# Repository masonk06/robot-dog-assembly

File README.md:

# Luca — RoboDog quadruped

A custom 3D-printed, 12-actuator quadruped built to investigate the path from
CAD and learned locomotion in simulation to calibrated physical motion.
This repository connects mechanical design, embedded telemetry, actuator
calibration, GPU reinforcement learning, and sim-to-real diagnostics.

**Current milestone:** slow walking in simulation and supported hardware
motion experiments. Full-body unsupported walking and closed-loop hardware
policy deployment are not yet validated.

[Sim-to-real comparison](#sim-to-real-evidence) ·
[Hardware and software](#hardware-and-software-stack) ·
[Calibration workflow](#calibration-and-hardware-workflow) ·
[Next steps](#next-engineering-milestones) ·
[Portfolio summary](docs/PORTFOLIO.md) ·
[Policy architecture](docs/POLICY_ARCHITECTURE.md)

## Ground-contact diagnostic — October 30, 2026

A 10-second excerpt at original speed from the temporary prototype's ground-contact
test. This records experimental stepping and contact behavior; unsupported walking
and closed-loop hardware policy deployment are not yet validated.
[Full diagnostic recording](docs/sim-to-real/raw/supported-ground-diagnostic-20261030.mov)

## Simulation and supported hardware comparison

[Watch the full comparison](docs/sim-to-real/simulation-vs-real.mp4) ·
[Recording context](docs/sim-to-real/README.md)

The simulation body is fixed and the physical robot is supported. The clips
are not phase-synchronized: they illustrate joint motion, not measured tracking
accuracy or unsupported walking.

## Engineering overview

The project follows a measurement-driven loop: build the mechanism, establish
joint correspondence, compare commanded and measured motion, identify model
gaps, and evaluate revised controllers in simulation before expanding hardware
tests.

- **Mechanical integration:** Fusion assemblies, printable geometry, placement
  tools, and successive electronics-packaging revisions.
- **Calibration and telemetry:** explicit servo IDs, model-zero captures,
  signed encoder correspondence, conservative limits, and a read-only live
  mirror between physical joints and the simulation.
- **Learning and simulation:** a four-beat reference gait with small learned
  residuals; MuJoCo/Newton validation and a CUDA PPO pipeline covering physics,
  observations, rewards, normalization, GAE, and optimizer updates.
- **Transfer diagnostics:** supported joint-tracking logs, IMU bring-up,
  controlled COM/contact experiments, and a separate robust quasi-static
  crawl development track.

### Results and validation boundaries

| Area | Recorded result | What remains unproven |
| --- | --- | --- |
| Preserved walking benchmark | About **16.02 cm forward in 20 s**, six steps per leg, with no falls/sliding resets across three simulation trials | Broad robustness or physical walking; this is a limited historical benchmark |
| GPU training | CUDA pipeline tested locally and on an OSU H100 allocation; selected checkpoints retain normalization and source archives | Training throughput alone does not establish gait quality or transfer |
| Supported hardware transfer | Rear-left IDs 8/9 progressed through small-angle and full-amplitude replay; the faster 46.2 s trial completed with verified torque release | All-leg calibration, ground balance, or feedback-policy deployment |
| IMU bring-up | ESP32 readout identified an MPU6500-compatible device; stationary reference and gyro-bias estimate saved | Full sensor calibration, robot-axis alignment, and policy-ready body-state estimation |
| Robust crawl | Separate simulation preset and scenario curriculum implemented | A validated robust-crawl result on the final robot |

The walking benchmark is documented in the [October 26 status snapshot](docs/STATUS.md)
and [preserved policies](policies/README.md). Later successor-policy diagnostics
have different conditions and should be read separately.

## Hardware and software stack

| Layer | Components and role |
| --- | --- |
| Mechanism | Custom printed quadruped, 12 STS3215 bus servos; Fusion snapshots and STL/STEP assets in [CAD](cad/README.md) |
| Servo bus | Waveshare Bus Servo Adapter (A), 12 V servo supply; historical PC serial tools and current ESP32 telemetry workflow |
| Embedded controller | NodeMCU ESP32S; servo UART on GPIO17 TX / GPIO16 RX; USB CSV telemetry normally on COM7 at 115200 baud |
| Inertial sensing | MPU6500-compatible device at I2C address 0x68, using GPIO21/22; [bring-up and reference capture](hardware/imu/README.md) |
| Calibration tools | Python viewers, timestamped zero/direction/limit records, encoder-to-model conversion, and read-only live mirroring |
| Simulation | MuJoCo robot model; Newton GPU physics and validation tools |
| Learning | PPO with a 60-value observation contract and 12 actions; 50 Hz control with learned residuals limited to about 2° in the preserved v7 controller |
| Reproducibility | Python 3.12, pinned CPU/CUDA dependency sets, W&B run tracking, frozen policy sources and normalization backups |

Final chassis, battery, power distribution, and onboard-compute integration
remain in development. Packaging CAD is revision-specific and does not
automatically update the simulation's mass, inertias, or joint geometry.

## Calibration and hardware workflow

Start with the [current hardware sequence](hardware/GETTING_DOG_RUNNING.md).
The newer ESP32 calibration records and older PC-driven rear-left replay
describe different stages of the prototype; historical successful motion
does not make the new frame ready for full-body replay.

1. **Confirm identity and zero pose.** Use the current joint map and
   [zero-point procedure](hardware/ESP32_ZERO_CHECK.md). Approximate model zeros
   live in [zero-points-current.json](hardware/calibrations/zero-points-current.json);
   they are not generic factory centers.
2. **Capture directions and conservative endpoints.** Follow the
   [ESP32 direction/limit checker](hardware/ESP32_DIRECTIONS_LIMITS.md), preserving
   timestamped evidence and the source-zero hash. Manual endpoint captures
   cover the checked neighboring poses, not every combined-leg configuration.
3. **Verify correspondence without commands.** Use the
   [read-only live mirror](hardware/READ_ONLY_LIVE_MIRROR.md), moving one
   torque-off joint by hand at a time. Confirm all 12 joints match the model.
4. **Review before powered replay.** Reconcile measured signs with command
   conversion and review non-wrapping limits and interference. The current
   telemetry CSV sketch is not an armed command transport; the ESP32 path still
   needs explicit arm/start/stop, fresh feedback, bounds, and a watchdog.
5. **Expand supported tests gradually.** Begin with one joint or one supported
   leg, record target/encoder response, and verify stop/release behavior.
   See the [historical supported replay](hardware/SUPPORTED_REPLAY.md) and
   [deployment handoff](hardware/SIM2REAL_HANDOFF.md) for context.

Current physical IDs, ordered hip roll / hip pitch / knee pitch:

| Leg | IDs |
| --- | --- |
| Front left | 4 / 5 / 6 |
| Front right | 1 / 2 / 3 |
| Rear left | 7 / 8 / 9 |
| Rear right | 11 / 10 / 12 |

The historical rear-left neutral is hip ID 8 = 1677 and knee ID 9 = 1572
ticks. Keep that record distinct from new-frame model-zero captures.
The receive-only tools do not arm motors or disable torque.

## Sim-to-real evidence

| Evidence | Engineering value | Interpretation boundary |
| --- | --- | --- |
| [Side-by-side animation and video](docs/sim-to-real/README.md) | Public visual comparison of successor-policy joint targets and supported robot motion | Fixed simulated body, supported robot, unaligned gait phases; no tracking metric |
| [Rear-left tracking records](reports/sim2real/README.md) | Commanded/measured ticks, error, temperature, and completion/release status for IDs 8/9 | Supported open-loop replay; no balance or world-motion measurement |
| [October 30 ground-contact diagnostic](docs/sim-to-real/raw/supported-ground-diagnostic-20261030.mov) | Records front-foot contact behavior on the temporary prototype | Diagnostic footage, not a validated walking demonstration |
| [COM/contact study](runs/com-dynamics-study/README.md) | Frozen policy and normalizer evaluated with identical three reset seeds across mass/COM scenarios | Simulation-only sensitivity study with provisional actuator/contact models |

In the COM study, the rear-biased case reduced front normal force by about
22% and triggered sliding resets in all three trials. A forward shift increased
front force but did not by itself produce a robust gait. The model has a lumped
base mass and no separate installed battery model, so this supports a hypothesis
about front-foot unloading rather than proving its physical cause.

That finding motivates the [quasi-static robust-crawl track](simulation/rl/QUASISTATIC_ROBUST_CRAWL.md):
a 5 s cycle, 5 mm/s command, 10 mm reference stride, 12 mm lift, and a 16% swing
fraction that schedules one swing leg and three stance legs. Its curriculum
varies COM, friction, and controller-response proxies across consecutive
simulation scenarios. Those proxies are not measured STS3215 dynamics, and
this workflow is not yet a hardware-validated policy.

## Next engineering milestones

1. **Close calibration gaps:** verify all 12 directions in the live mirror,
   capture conservative endpoints, reconcile historical mappings, and review
   a canonical calibration before generating new motion commands.
2. **Identify actuator response:** measure supported step-response tracking,
   latency, and rate behavior; use the measurements to replace provisional
   controller-response ranges.
3. **Model the final assembly:** measure installed component masses and
   locations, separate frame/electronics/battery inertias, and re-evaluate COM
   and contact sensitivity.
4. **Evaluate crawl robustness:** test saved candidates across the corrected
   model and declared COM/friction/actuator scenarios, reporting progress,
   slip, pitch, and failures alongside the test conditions.
5. **Complete the hardware feedback path:** align and calibrate the mounted
   IMU, supply the policy's body-state observations, and implement guarded
   command transport before a staged supported-to-ground progression.

## Explore the repository

| Folder or guide | Contents |
| --- | --- |
| [cad](cad/README.md) | Mechanical snapshots, build tools, printable assets and revision context |
| [hardware](hardware/README.md) | Servo mapping, calibration history, telemetry, IMU and supported replay |
| [simulation/mujoco](simulation/mujoco/README.md) | Robot model, scripted previews and model checks |
| [simulation/rl](simulation/rl/README.md) | Controller contract, CPU/Newton validation, CUDA PPO and evaluation |
| [policies](policies/README.md) | Selected milestones with weights, normalization and exact training sources |
| [reports/sim2real](reports/sim2real/README.md) | Representative supported tracking records |
| [runs/com-dynamics-study](runs/com-dynamics-study/README.md) | Controlled COM/contact comparison and limitations |
| [HPC guide](docs/HPC.md) | Environments, continuation and checkpoint handling |

## Local setup and simulation playback

Use Python 3.12. From the repository root:

```bash
python -m venv .venv
# Activate the environment for your shell.
python -m pip install -r requirements-rl.txt
python -m pytest -q
```

`pytest.ini` selects simulation and mock hardware tests; it does not run motor
experiments. Read the hardware guide before executing standalone hardware
scripts, which may contain serial actions or historical hardcoded IDs.

## Clone on another laptop / Codex

```powershell
git clone https://github.com/masonk06/robot-dog-assembly.git
cd robot-dog-assembly
py -3.12 -m venv .venv
.\.venv\Scripts\Activate.ps1
python -m pip install -r requirements-rl.txt
python -m pytest -q
```

Start by reading [docs/STATUS.md](docs/STATUS.md), then the relevant folder's
README. Simulation and code review are safe laptop tasks. Hardware scripts only
connect or move servos when supplied an explicit serial port and `--execute`;
do not run them merely to inspect the repository. The current four-leg power
distribution revision is **not approved for fabrication**; see
[revision_four_leg/README.md](revision_four_leg/README.md).

For a compatible NVIDIA system, use the separate pinned
`requirements-cuda.txt` environment and follow [CUDA training](simulation/rl/CUDA_TRAINING.md)
and the [HPC guide](docs/HPC.md). In a Newton-capable environment, play the
preserved best-distance checkpoint:

```bash
python simulation/rl/play.py policies/best-distance --source simulation/mujoco
```

Preserve normalization with weights and keep new runs separate from milestone
backups.

## Asset and backup scope

Git contains selected code, CAD exports, calibration history, representative
measurements, and policy/source backups. Full raw training runs, environments,
caches, transfer archives, and containers are excluded. Unsaved Fusion state
and unexported remote HPC files are outside this backup.

No license has been selected. Third-party geometry retains its ownership and terms.

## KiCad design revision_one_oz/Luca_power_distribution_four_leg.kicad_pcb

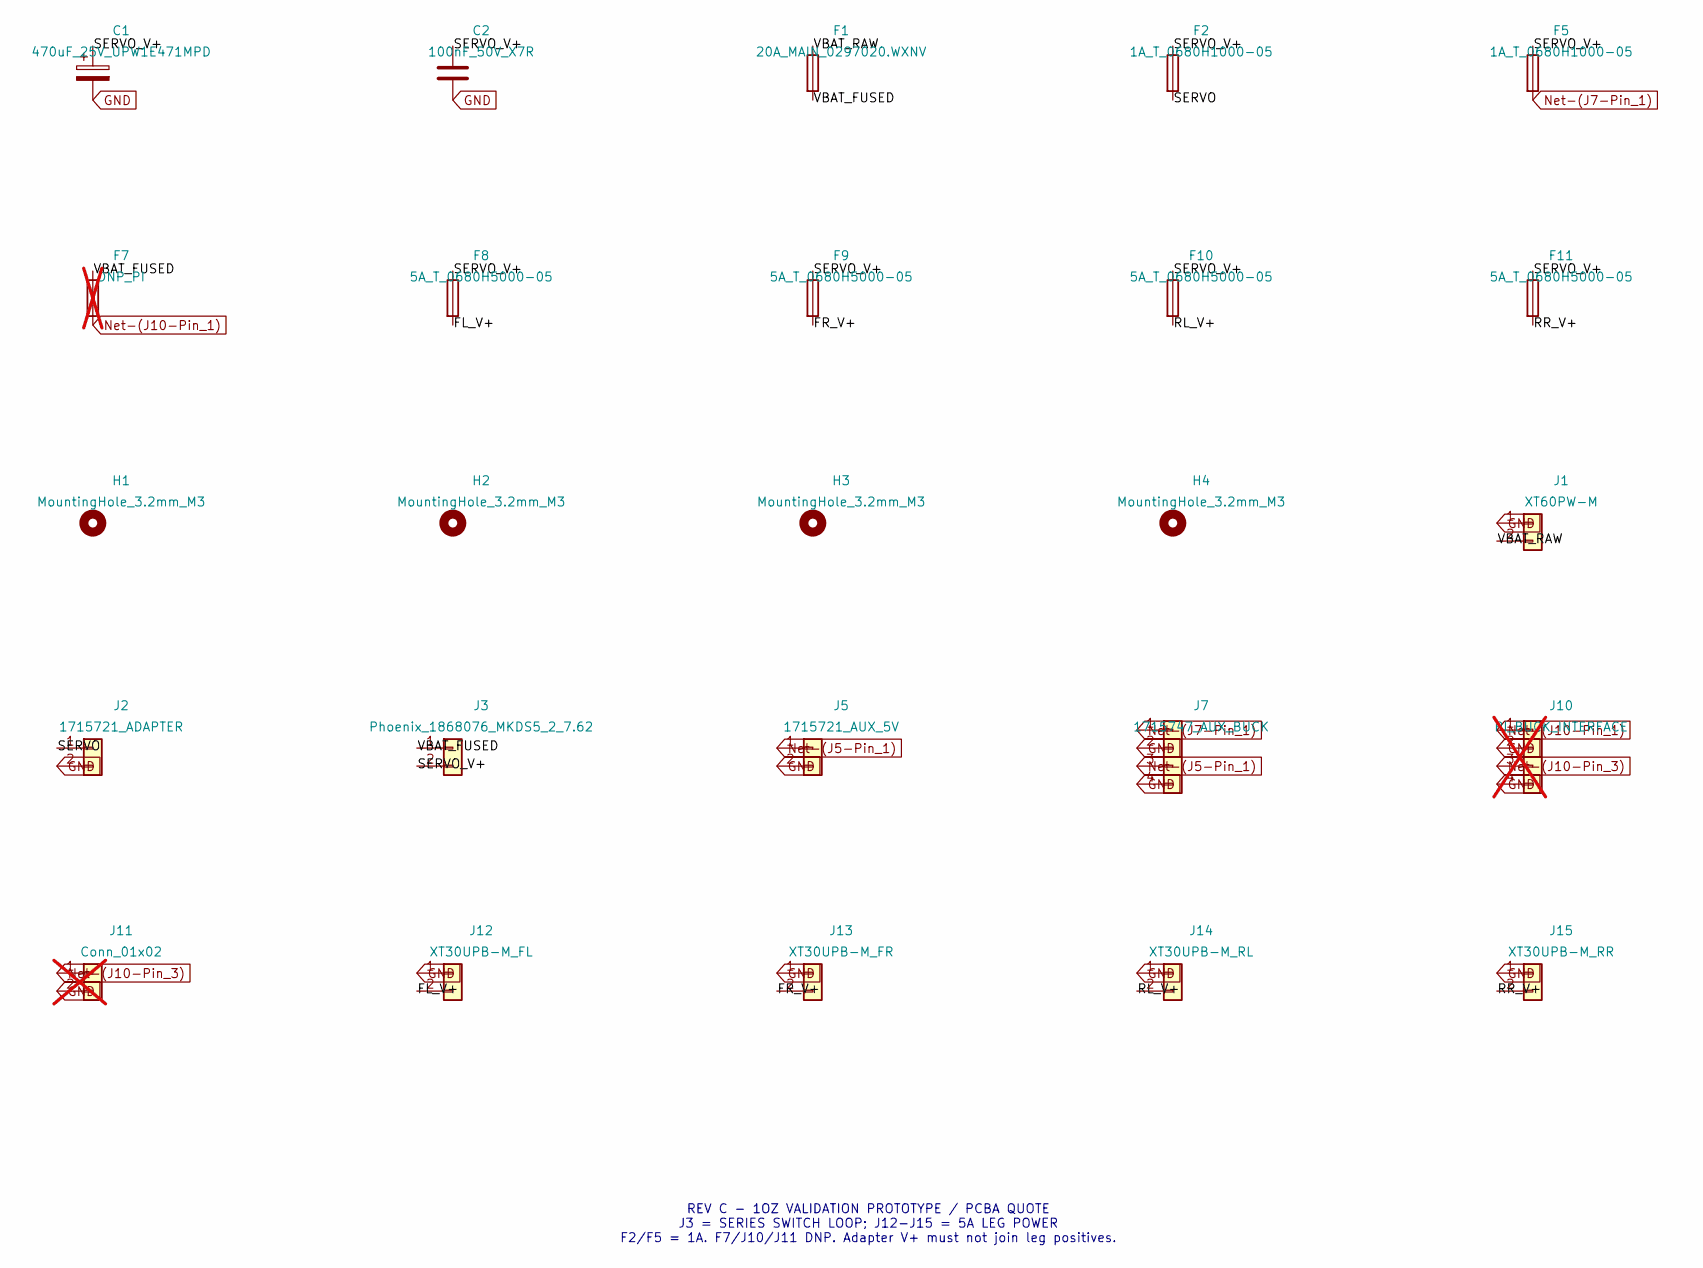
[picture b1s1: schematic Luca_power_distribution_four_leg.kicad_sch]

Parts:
C1: 470uF_25V_UPW1E471MPD; CP_Radial_D10.0mm_P5.00mm
C2: 100nF_50V_X7R; C_0805_2012Metric
F1: 20A_MAIN_0297020.WXNV; Fuseholder_Blade_Mini_Keystone_3568
F2, F5: 1A_T_0680H1000-05; Bel_0680H_2410_Recommended
F7: DNP_PI; Bel_0680H_2410_DNP_NoPaste; not fitted
F8, F9, F10, F11: 5A_T_0680H5000-05; Bel_0680H_2410_Recommended
H1, H2, H3, H4: MountingHole_3.2mm_M3
J1: XT60PW-M; AMASS_XT60PW_M_ReinforcedTabs
J2: 1715721_ADAPTER; TerminalBlock_Phoenix_MKDS-1,5-2-5.08_1x02_P5.08mm_Horizont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
J3: Phoenix_1868076_MKDS5_2_7.62; Phoenix_MKDS5_2_7.62_1868076
J5: 1715721_AUX_5V; TerminalBlock_Phoenix_MKDS-1,5-2-5.08_1x02_P5.08mm_Horizont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
J7: 1715747_AUX_BUCK; TerminalBlock_Phoenix_MKDS-1,5-4-5.08_1x04_P5.08mm_Horizont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
J10: PI_BUCK_INTERFACE; TerminalBlock_Phoenix_MKDS-1,5-4-5.08_1x04_P5.08mm_Horizont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; not fitted
J11: Conn_01x02; TerminalBlock_Phoenix_MKDS-1,5-2-5.08_1x02_P5.08mm_Horizont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; not fitted
J12: XT30UPB-M_FL; AMASS_XT30UPB-M_1x02_P5.0mm_Vertical
J13: XT30UPB-M_FR; AMASS_XT30UPB-M_1x02_P5.0mm_Vertical
J14: XT30UPB-M_RL; AMASS_XT30UPB-M_1x02_P5.0mm_Vertical
J15: XT30UPB-M_RR; AMASS_XT30UPB-M_1x02_P5.0mm_Vertical

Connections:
/FL_V+: F8.2, J12.2
/FR_V+: F9.2, J13.2
/RL_V+: F10.2, J14.2
/RR_V+: F11.2, J15.2
/SERVO: F2.2, J2.1
/SERVO_V+: C1.1, C2.1, F2.1, F5.1, F8.1, F9.1, F10.1, F11.1, J3.2
/VBAT_FUSED: F1.2, F7.1, J3.1
/VBAT_RAW: F1.1, J1.2
GND: C1.2, C2.2, J1.1, J2.2, J5.2, J7.2, J7.4, J10.2, J10.4, J11.2, J12.1, J13.1, J14.1, J15.1
unnamed: J5.1, J7.3
unnamed: F5.2, J7.1
unnamed: F7.2, J10.1
unnamed: J10.3, J11.1

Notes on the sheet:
REV C - 1OZ VALIDATION PROTOTYPE / PCBA QUOTE J3 = SERIES SWITCH LOOP; J12-J15 = 5A LEG POWER F2/F5 = 1A. F7/J10/J11 DNP. Adapter V+ must not join leg positives.

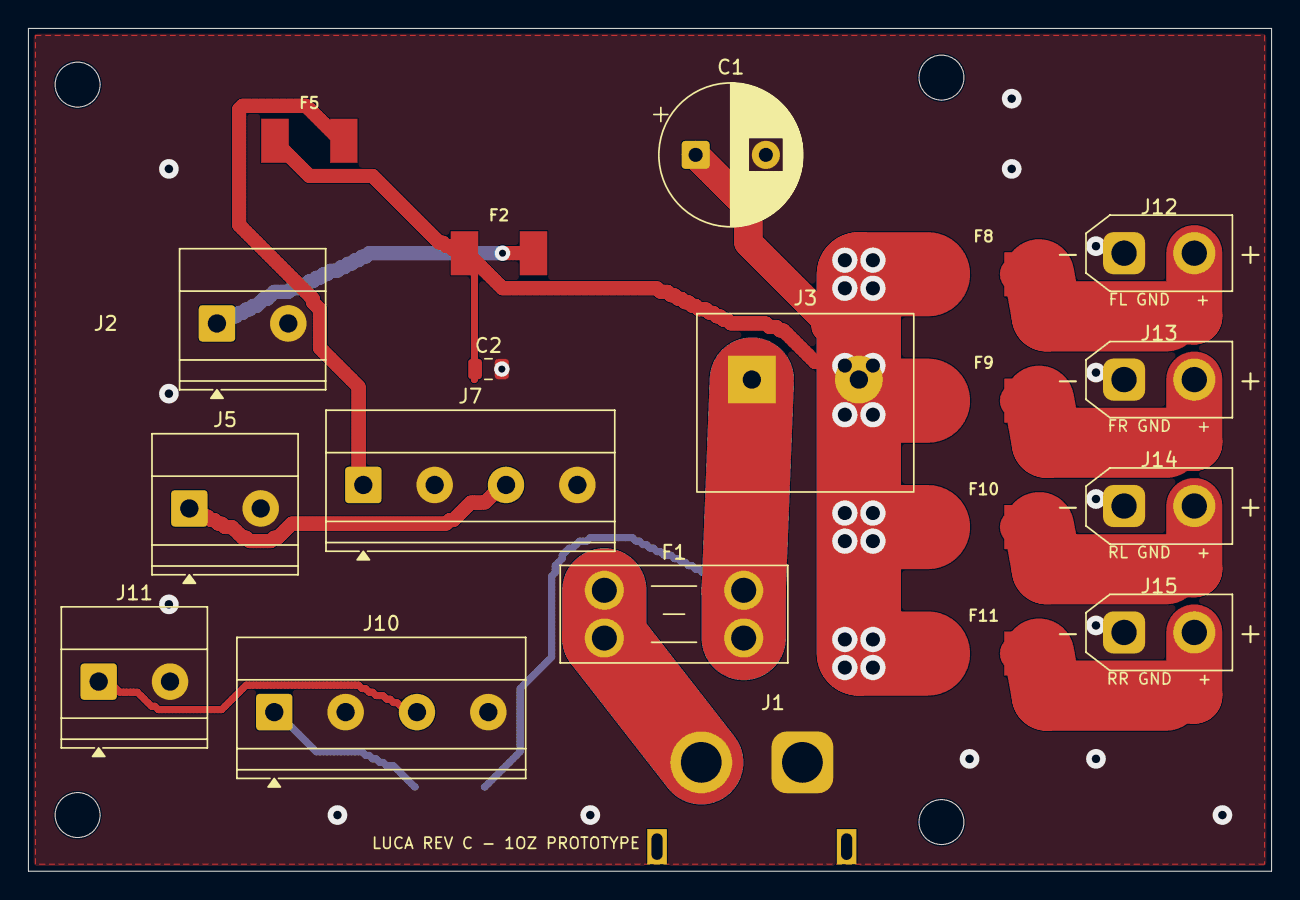
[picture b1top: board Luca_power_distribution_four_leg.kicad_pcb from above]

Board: 2 copper layers, 88.5 x 60.0 mm, 25 parts (1 on the bottom side), 13 nets.

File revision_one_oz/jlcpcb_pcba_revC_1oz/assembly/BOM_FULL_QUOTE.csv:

Comment,Designator,Footprint,LCSC Part #,Manufacturer,Manufacturer Part Number,Quantity,Description
UPW1E471MPD,C1,Capacitor_THT:CP_Radial_D10.0mm_P5.00mm,C433175,Nichicon,UPW1E471MPD,1,470uF 25V 105C radial D10x16 P5mm
CL21B104KBCNNNC,C2,Capacitor_SMD:C_0805_2012Metric,C1711,Samsung Electro-Mechanics,CL21B104KBCNNNC,1,100nF 50V X7R 10% 0805
3568,F1,Fuse:Fuseholder_Blade_Mini_Keystone_3568,,Keystone Electronics,3568,1,MINI blade fuse holder ONLY; insert separate 20A fuse after inspection
0680H1000-05,"F2,F5",Luca_Review:Bel_0680H_2410_Recommended,,Bel Fuse,0680H1000-05,2,1A slow-blow 125VDC 2410
0680H5000-05,"F8,F9,F10,F11",Luca_Review:Bel_0680H_2410_Recommended,,Bel Fuse,0680H5000-05,4,5A slow-blow 125VDC 2410
XT60PW-M,J1,Luca_Review:AMASS_XT60PW_M_ReinforcedTabs,C98732,Changzhou Amass Electronics,XT60PW-M,1,PCB mount right-angle XT60 male; verify 2025V0 XT60PW-M30.G.Y.T drawing
1715721,"J2,J5","TerminalBlock_Phoenix:TerminalBlock_Phoenix_MKDS-1,5-2-5.08_1x02_P5.08mm_Horizontal",,Phoenix Contact,1715721,2,MKDS 1.5/2-5.08 2-pin terminal
1868076,J3,Luca_Review:Phoenix_MKDS5_2_7.62_1868076,,Phoenix Contact,1868076,1,MKDS 5/2-7.62 high-current switch-loop terminal
1715747,J7,"TerminalBlock_Phoenix:TerminalBlock_Phoenix_MKDS-1,5-4-5.08_1x04_P5.08mm_Horizontal",,Phoenix Contact,1715747,1,MKDS 1.5/4-5.08 external AUX buck interface
XT30UPB-M,"J12,J13,J14,J15",Connector_AMASS:AMASS_XT30UPB-M_1x02_P5.0mm_Vertical,C428721,Changzhou Amass Electronics,XT30UPB-M,4,Vertical PCB XT30; pad1 negative pad2 positive

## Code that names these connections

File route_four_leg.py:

import route_board as r
from pathlib import Path
p=r.p
root=Path(__file__).parent/'revision_four_leg';target=root/'Luca_power_distribution_four_leg.kicad_pcb'
r.b=p.LoadBoard(str(target));r.pads=list(r.b.GetPads());r.tracks=[];r.mask_cache.clear();r.margin=.45
r.xmax=198.5;r.nx=355
r.xx,r.yy=r.np.meshgrid(r.xmin+r.np.arange(r.nx)*r.step,r.ymin+r.np.arange(r.ny)*r.step,indexing='ij')
for t in list(r.b.GetTracks()):r.b.Remove(t)
legs=[r.b.FindNet('/'+leg+'_V+').GetNetCode() for leg in ('FL','FR','RL','RR')]
names=['/VBAT_RAW','/VBAT_FUSED','/SERVO','/SERVO_V+','Net-(J7-Pin_1)','Net-(J10-Pin_1)','Net-(J5-Pin_1)','Net-(J10-Pin_3)','GND']
codes={name:r.b.FindNet(name).GetNetCode() for name in names}
order=legs+[codes[name] for name in names]
wide=legs+[codes[name] for name in ['/VBAT_RAW','/VBAT_FUSED','/SERVO','/SERVO_V+','GND']]
missing=[]
for n in order:
 pp=[q for q in r.pads if q.GetNetCode()==n]
 if not pp:continue
 pp.sort(key=lambda q:(q.GetAttribute()==p.PAD_ATTRIB_SMD,q.GetParentFootprint().GetReference().startswith('C')))
 name=r.b.FindNet(n).GetNetname()
 if name in ('/SERVO_V+','/VBAT_FUSED'):pp.sort(key=lambda q:q.GetParentFootprint().GetReference()!='J3')
 if name in ('/VBAT_RAW','GND'):pp.sort(key=lambda q:q.GetParentFootprint().GetReference()!='J1')
 connected=[pp.pop(0)]
 while pp:
  choices=sorted((r.math.dist(r.xy(a),r.xy(c))+(500 if c.GetParentFootprint().GetReference()=='C2' else 0),i,j) for i,a in enumerate(connected) for j,c in enumerate(pp) if a.GetParentFootprint().GetReference()!='C2')
  found=None
  for _,i,j in choices:
   a,c=connected[i],pp[j];w=3 if n in wide else 1
   # Keep wide supply trunks off B.Cu. Bottom SMD input pads receive a local
   # via transition in the second routing stage instead of a long B.Cu trunk.
   if n in wide and name!='GND' and any(q.GetAttribute()==p.PAD_ATTRIB_SMD and q.IsOnLayer(p.B_Cu) for q in (a,c)):continue
   if a.GetParentFootprint().GetReference()=='C2' or c.GetParentFootprint().GetReference()=='C2':w=.5
   candidate_layers=(p.B_Cu,p.F_Cu) if name=='GND' else (p.F_Cu,)
   if a.GetAttribute()==p.PAD_ATTRIB_SMD and a.IsOnLayer(p.B_Cu) or c.GetAttribute()==p.PAD_ATTRIB_SMD and c.IsOnLayer(p.B_Cu):candidate_layers=(p.B_Cu,)
   for layer in candidate_layers:
    if not a.IsOnLayer(layer) or not c.IsOnLayer(layer):continue
    result=r.route(r.xy(a),r.xy(c),n,w,layer)
    if result:found=(result[0],w,layer,j);break
   if found:break
  if not found:
   missing.append((n,[(q.GetParentFootprint().GetReference(),q.GetNumber()) for q in pp]));break
  pts,w,layer,j=found;r.commit(pts,n,w,layer);connected.append(pp.pop(j));print('routed',n,w,layer,flush=True)
p.SaveBoard(str(target),r.b)
print('UNFINISHED',missing,flush=True)
